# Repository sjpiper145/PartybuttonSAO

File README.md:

# PartybuttonSAO
SAO PCB Badge for the 2022 Linux Conference Aus

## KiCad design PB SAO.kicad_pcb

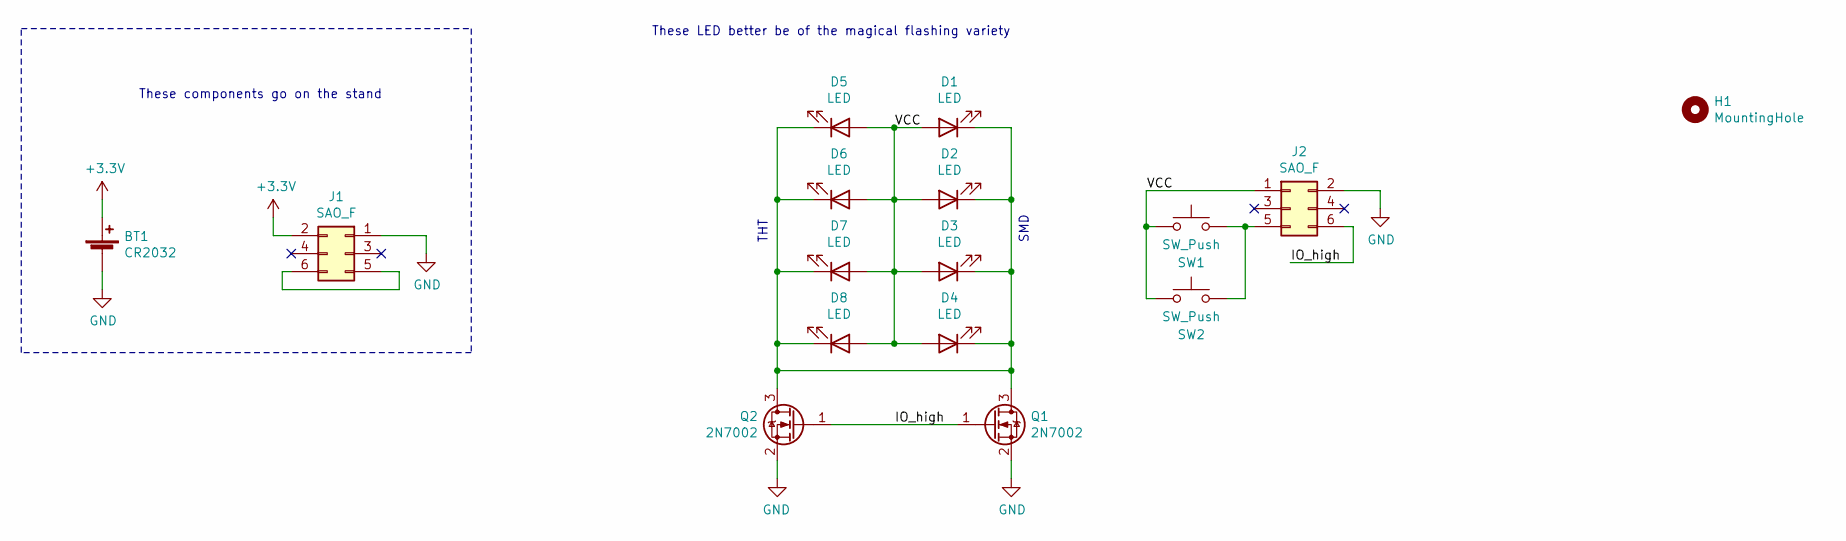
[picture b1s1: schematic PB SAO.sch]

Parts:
BT1: CR2032; BatteryHolder_Keystone_3034_1x20mm
D1, D2, D3, D4: LED; LED_0805_2012Metric_Pad1.15x1.40mm_HandSolder
D5, D6, D7, D8: LED; LED_D3.0mm
H1: MountingHole; MountingHole_3mm
J1, J2: SAO_F; PinHeader_2x03_P2.54mm_Vertical
Q1: 2N7002; SOT-23_Handsoldering
Q2: 2N7002; TO-92
SW1: SW_Push; SW_PUSH_6mm
SW2: SW_Push; SW_Push_1P1T_NO_6x6mm_H9.5mm

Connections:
+3V3: BT1.1 (+), J1.2
/IO_high: J2.6, Q1.1 (G), Q2.1 (G)
/VCC: D1.2 (A), D2.2 (A), D3.2 (A), D4.2 (A), D5.2 (A), D6.2 (A), D7.2 (A), D8.2 (A), J2.1, SW1.1, SW2.1
GND: BT1.2 (-), J1.1, J2.2, Q1.2 (S), Q2.2 (S)
unnamed: D1.1 (K), D2.1 (K), D3.1 (K), D4.1 (K), D5.1 (K), D6.1 (K), D7.1 (K), D8.1 (K), Q1.3 (D), Q2.3 (D)
unnamed: J1.5, J1.6
unnamed: J2.5, SW1.2, SW2.2

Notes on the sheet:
These components go on the stand
These LED better be of the magical flashing variety
SMD
THT

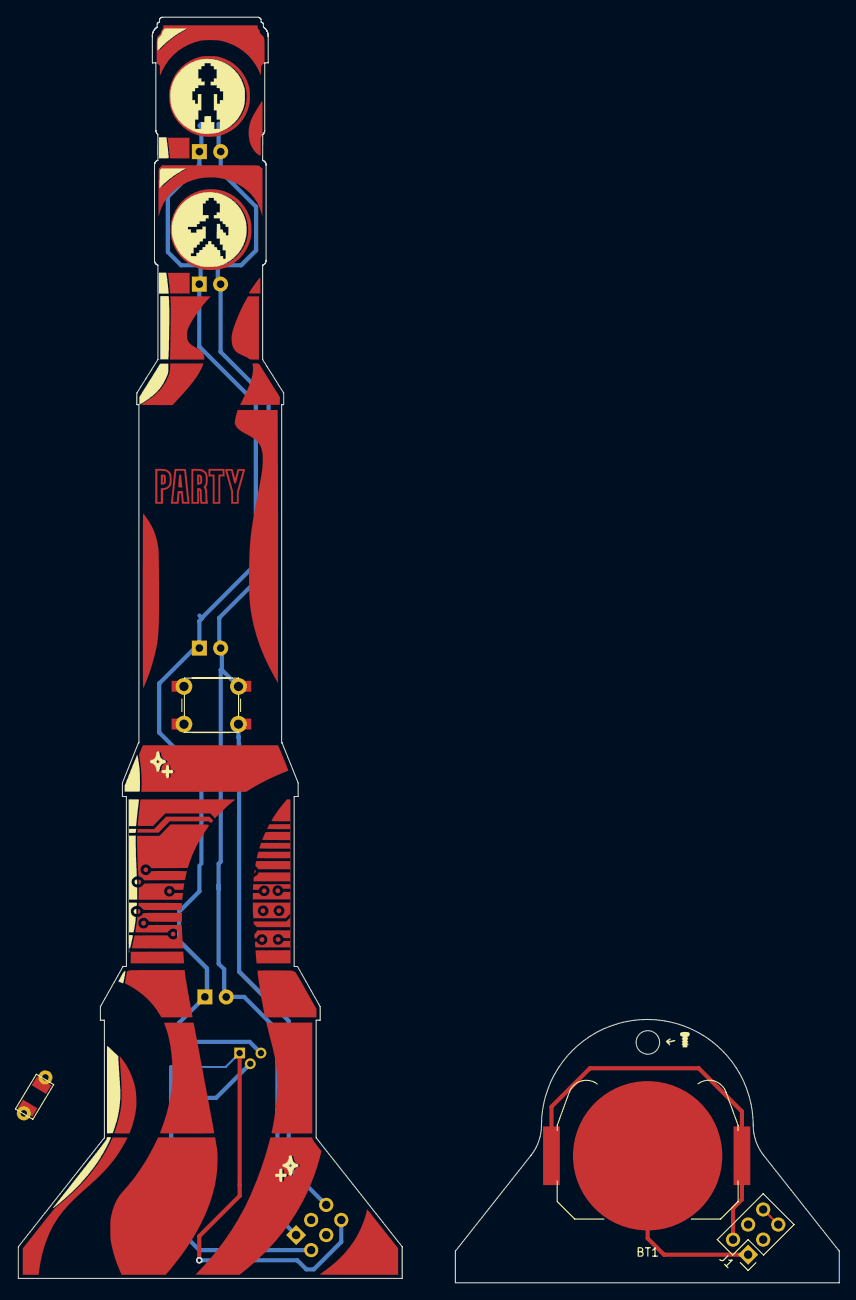
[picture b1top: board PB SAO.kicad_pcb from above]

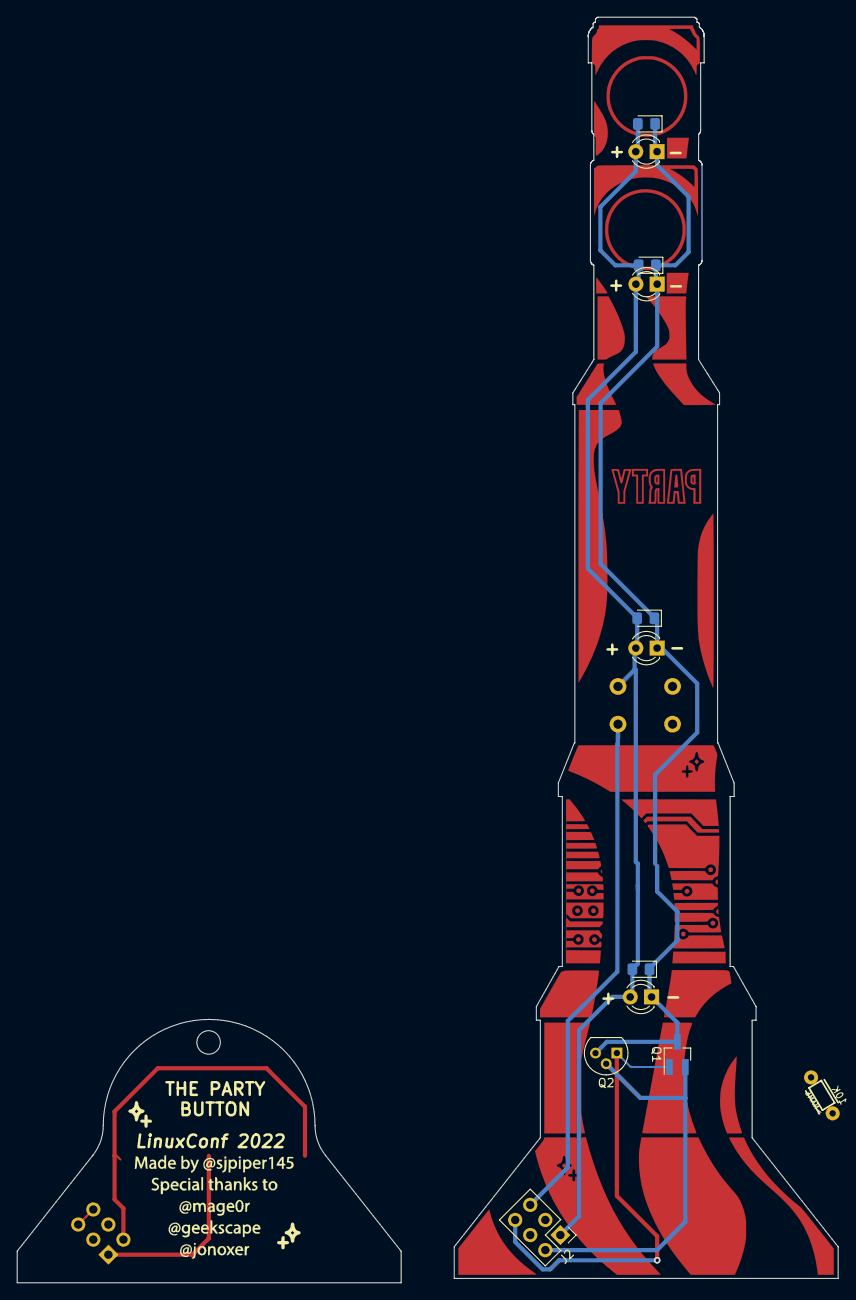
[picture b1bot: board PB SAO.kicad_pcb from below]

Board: 2 copper layers, 45.8 x 150.3 mm, 18 parts (11 on the bottom side), 7 nets.

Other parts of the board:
>NAME: 10K; 1210
>NAME#2: >VALUE; 1_6W-RES

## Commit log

2021-10-17 Add files via upload
    V2 including Mag0r's edits.
